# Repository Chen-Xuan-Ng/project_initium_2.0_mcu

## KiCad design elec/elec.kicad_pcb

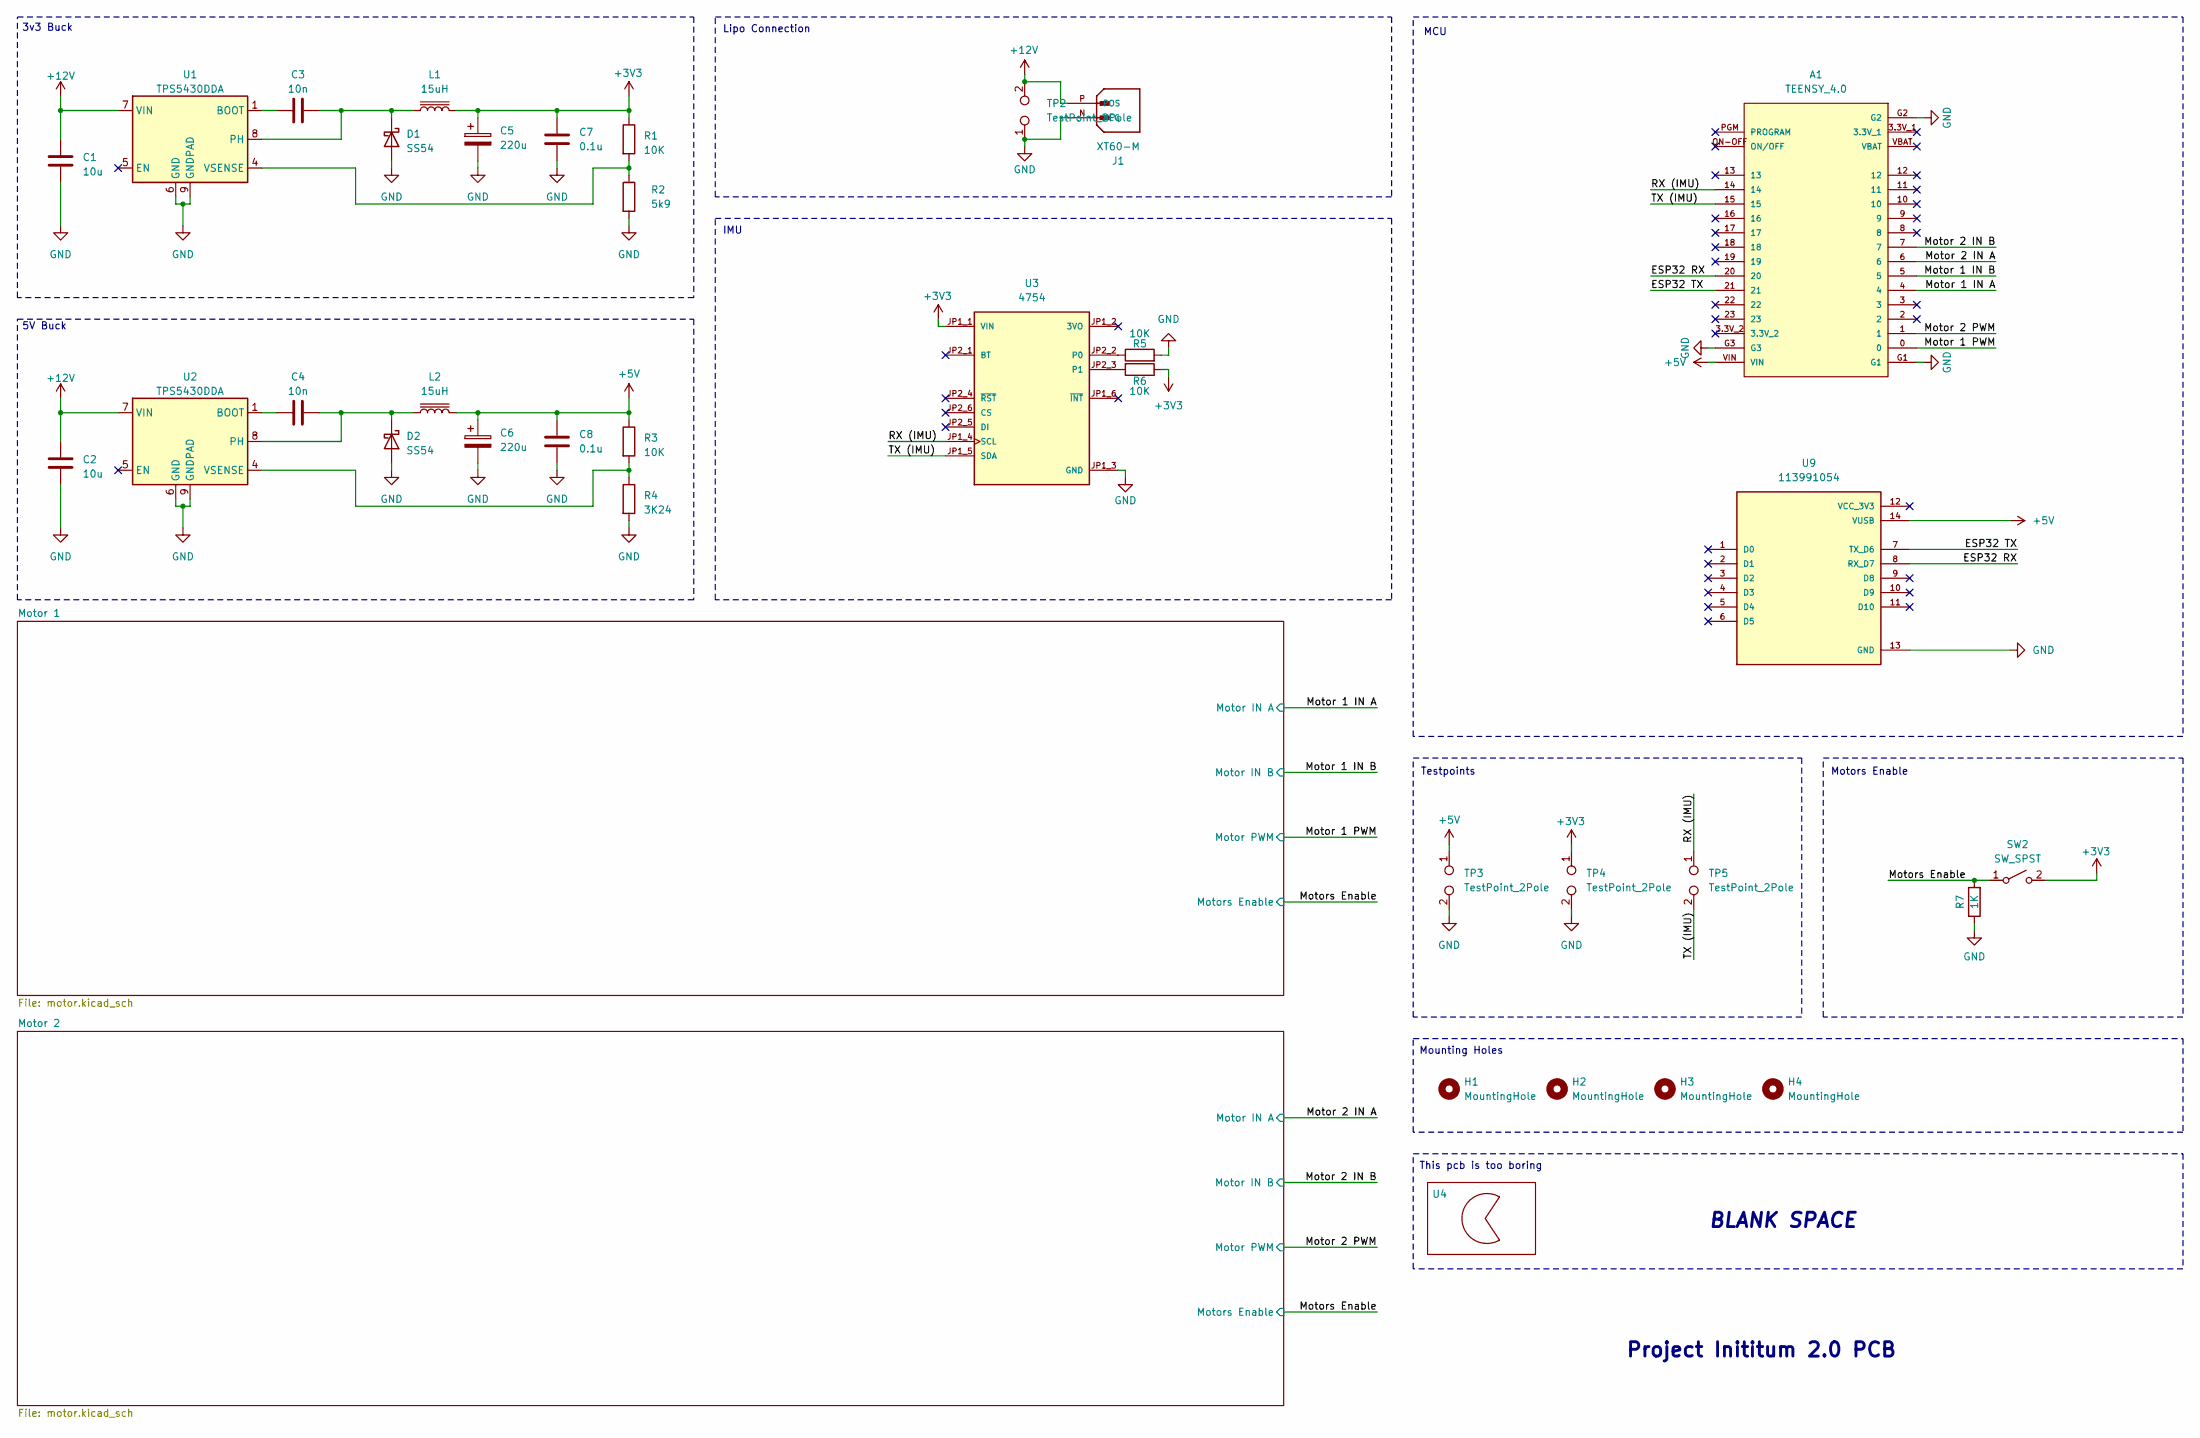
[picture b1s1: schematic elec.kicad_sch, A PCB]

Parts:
A1: TEENSY_4.0; MODULE_DEV-15583
C1, C2: 10u; C_0603_1608Metric; LCSC C92487
C3, C4: 10n; C_0603_1608Metric; LCSC C597236
C5, C6: 220u; CP_EIA-7343-15_Kemet-W_Pad2.25x2.55mm_HandSolder; LCSC C5348248
C7, C8: 0.1u; C_0603_1608Metric; LCSC C577419
D1, D2: SS54; DIOM5025X220N; LCSC C6807781
H1, H2, H3, H4: MountingHole; MountingHole_3.2mm_M3_Pad
J1: XT60-M; AMASS_XT60-M_1x02_P7.20mm_Vertical; PARTREV V1.2
L1, L2: 15uH; L_APV_APH1040; LCSC C5189959
R1, R3: 10K; R_0603_1608Metric; LCSC C25804
R2: 5k9; R_0603_1608Metric; LCSC C22994
R4: 3K24; R_0603_1608Metric; LCSC C22994
R5, R6: 10K; R_0603_1608Metric
R7: 1K; R_0603_1608Metric
SW2: SW_SPST; JST_XH_B2B-XH-A_1x02_P2.50mm_Vertical
TP2, TP3, TP4, TP5: TestPoint_2Pole; TestPoint_2Pads_Pitch2.54mm_Drill0.8mm
U1, U2: TPS5430DDA; TI_SO-PowerPAD-8; LCSC C9864
U3: 4754; MODULE_4754; PARTREV 2021-03-16
U4: pacman
U9: 113991054; XiaoSeeedStudioEsp32; PARTREV 23/05/2022

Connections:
+3V3: C5.1, C7.1, L1.2, R1.1, R6.1, SW2.2 (B), TP4.1, U3.JP1_1 (VIN); also elsewhere on the board
+5V: A1.VIN, C6.1, C8.1, L2.2, R3.1, TP3.1, U9.14 (VUSB)
+12V: C1.1, C2.1, J1.P (POS), TP2.2, U1.7 (VIN), U2.7 (VIN); also elsewhere on the board
/ESP32 RX: A1.20, U9.8 (RX_D7)
/ESP32 TX: A1.21, U9.7 (TX_D6)
/Motor 1 IN A: A1.4; also elsewhere on the board
/Motor 1 IN B: A1.5; also elsewhere on the board
/Motor 1 PWM: A1.0; also elsewhere on the board
/Motor 2 IN A: A1.6; also elsewhere on the board
/Motor 2 IN B: A1.7; also elsewhere on the board
/Motor 2 PWM: A1.1; also elsewhere on the board
/Motors Enable: R7.2, SW2.1 (A); also elsewhere on the board
/RX (IMU): A1.14, TP5.1, U3.JP1_4 (SCL)
/TX (IMU): A1.15, TP5.2, U3.JP1_5 (SDA)
GND: A1.G1, A1.G2, A1.G3, C1.2, C2.2, C5.2, C6.2, C7.2, C8.2, D1.2 (A), D2.2 (A), J1.N (NEG), R2.2, R4.2, R5.2, R7.1, TP2.1, TP3.2, TP4.2, U1.6 (GND), U1.9 (GNDPAD), U2.6 (GND), U2.9 (GNDPAD), U3.JP1_3 (GND), U9.13 (GND); also elsewhere on the board
unnamed: C3.2, D1.1 (K), L1.1, U1.8 (PH)
unnamed: C4.2, D2.1 (K), L2.1, U2.8 (PH)
unnamed: C3.1, U1.1 (BOOT)
unnamed: R1.2, R2.1, U1.4 (VSENSE)
unnamed: C4.1, U2.1 (BOOT)
unnamed: R3.2, R4.1, U2.4 (VSENSE)
unnamed: R5.1, U3.JP2_2 (P0)
unnamed: R6.2, U3.JP2_3 (P1)

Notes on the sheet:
Testpoints
IMU
3v3 Buck
5V Buck
Lipo Connection
MCU
Mounting Holes
Project Inititum 2.0 PCB
Motors Enable
This pcb is too boring
BLANK SPACE

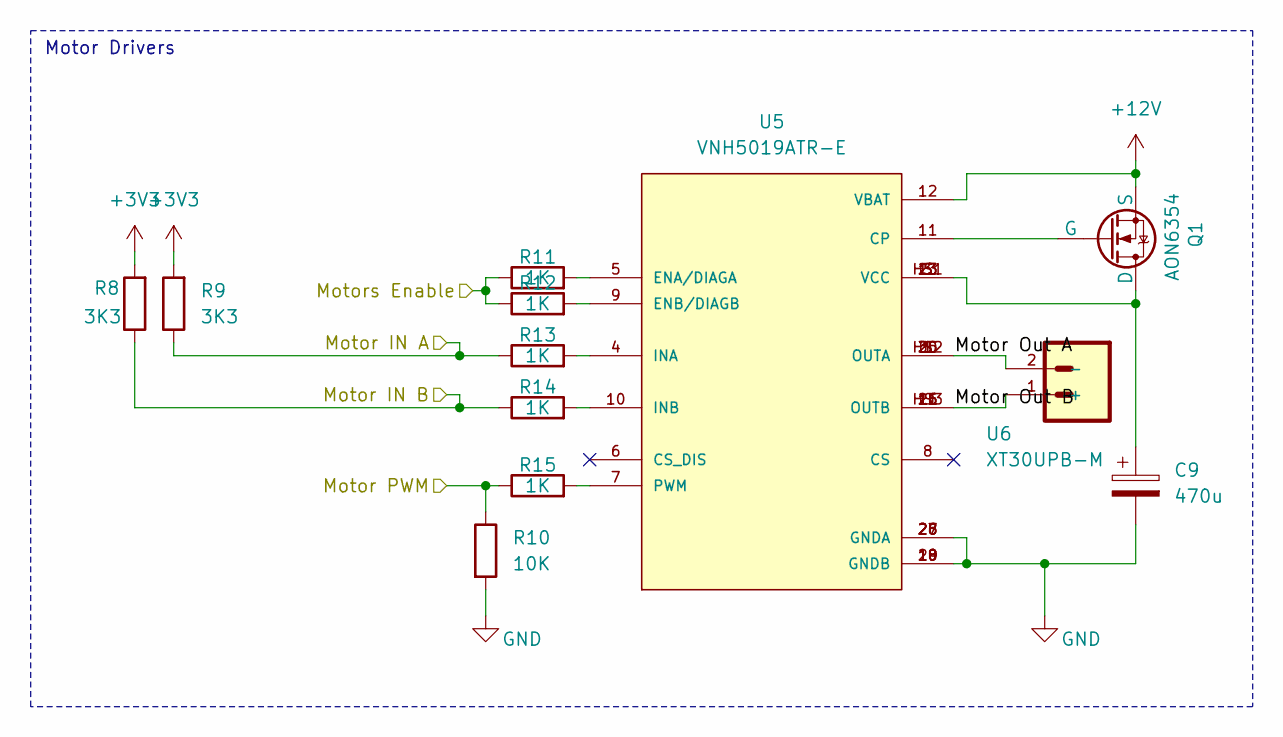
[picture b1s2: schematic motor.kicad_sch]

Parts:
C9: 470u; CP_Radial_D8.0mm_P3.50mm; LCSC C5162352
Q1: AON6354; 8-DFN (5x6)
R8, R9: 3K3; R_0603_1608Metric
R10: 10K; R_0603_1608Metric
R11, R12, R13, R14, R15: 1K; R_0603_1608Metric
U5: VNH5019ATR-E; PARTREV 11
U6: XT30UPB-M; AMASS_XT30UPB-M_1x02_P5.0mm_Vertical

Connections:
+3V3: R8.2, R9.2; also elsewhere on the board
+12V: Q1.1 (S), Q1.2 (S), Q1.3 (S), U5.12 (VBAT); also elsewhere on the board
/Motor 1 IN A: R9.1, R13.1; also elsewhere on the board
/Motor 1 IN B: R8.1, R14.1; also elsewhere on the board
/Motor 1 PWM: R10.1, R15.1; also elsewhere on the board
/Motor 1/Motor Out A: U5.1 (OUTA), U5.25 (OUTA), U5.30 (OUTA), U5.HS2 (OUTA), U6.2 (-)
/Motor 1/Motor Out B: U5.15 (OUTB), U5.16 (OUTB), U5.21 (OUTB), U5.HS3 (OUTB), U6.1 (+)
/Motors Enable: R11.1, R12.1; also elsewhere on the board
GND: C9.2, R10.2, U5.18 (GNDB), U5.19 (GNDB), U5.20 (GNDB), U5.26 (GNDA), U5.27 (GNDA), U5.28 (GNDA); also elsewhere on the board
unnamed: C9.1, Q1.5 (D), Q1.6 (D), Q1.7 (D), Q1.8 (D), Q1.9 (D), U5.3 (VCC), U5.13 (VCC), U5.23 (VCC), U5.HS1 (VCC)
unnamed: Q1.4 (G), U5.11 (CP)
unnamed: R11.2, U5.5 (ENA/DIAGA)
unnamed: R12.2, U5.9 (ENB/DIAGB)
unnamed: R13.2, U5.4 (INA)
unnamed: R14.2, U5.10 (INB)
unnamed: R15.2, U5.7 (PWM)

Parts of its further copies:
C10: 470u; CP_Radial_D8.0mm_P3.50mm; LCSC C5162352
Q2: AON6354; 8-DFN (5x6)
R16, R17: 3K3; R_0603_1608Metric
R18: 10K; R_0603_1608Metric
R19, R20, R21, R22, R23: 1K; R_0603_1608Metric
U7: VNH5019ATR-E; PARTREV 11
U8: XT30UPB-M; AMASS_XT30UPB-M_1x02_P5.0mm_Vertical

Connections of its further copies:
+3V3: R16.2, R17.2; also elsewhere on the board
+12V: Q2.1 (S), Q2.2 (S), Q2.3 (S), U7.12 (VBAT); also elsewhere on the board
/Motor 2 IN A: R17.1, R21.1; also elsewhere on the board
/Motor 2 IN B: R16.1, R22.1; also elsewhere on the board
/Motor 2 PWM: R18.1, R23.1; also elsewhere on the board
/Motor 2/Motor Out A: U7.1 (OUTA), U7.25 (OUTA), U7.30 (OUTA), U7.HS2 (OUTA), U8.2 (-)
/Motor 2/Motor Out B: U7.15 (OUTB), U7.16 (OUTB), U7.21 (OUTB), U7.HS3 (OUTB), U8.1 (+)
/Motors Enable: R19.1, R20.1; also elsewhere on the board
GND: C10.2, R18.2, U7.18 (GNDB), U7.19 (GNDB), U7.20 (GNDB), U7.26 (GNDA), U7.27 (GNDA), U7.28 (GNDA); also elsewhere on the board
unnamed: C10.1, Q2.5 (D), Q2.6 (D), Q2.7 (D), Q2.8 (D), Q2.9 (D), U7.3 (VCC), U7.13 (VCC), U7.23 (VCC), U7.HS1 (VCC)
unnamed: Q2.4 (G), U7.11 (CP)
unnamed: R19.2, U7.5 (ENA/DIAGA)
unnamed: R20.2, U7.9 (ENB/DIAGB)
unnamed: R21.2, U7.4 (INA)
unnamed: R22.2, U7.10 (INB)
unnamed: R23.2, U7.7 (PWM)

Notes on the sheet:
Motor Drivers

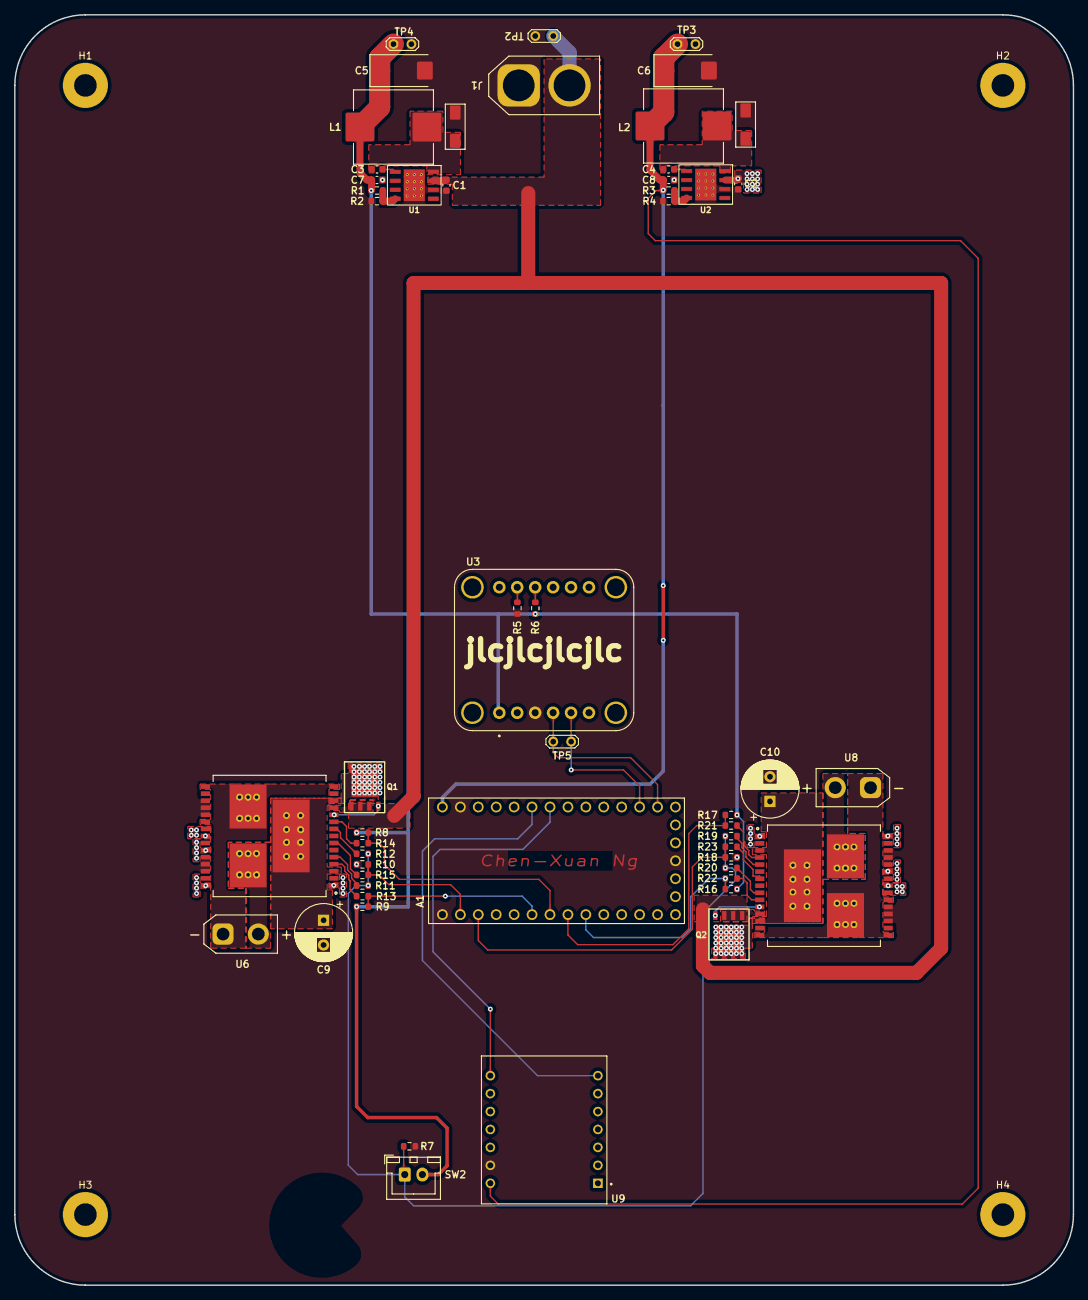
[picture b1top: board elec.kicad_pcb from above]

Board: 2 copper layers, 150.0 x 180.0 mm, 59 parts (0 on the bottom side), 41 nets.

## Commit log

2025-06-18 completed?
2025-06-18 3 renders, why is the last one taking so long
2025-06-19 uploaded print files
2025-06-20 added lazercutting
2025-07-22 code
